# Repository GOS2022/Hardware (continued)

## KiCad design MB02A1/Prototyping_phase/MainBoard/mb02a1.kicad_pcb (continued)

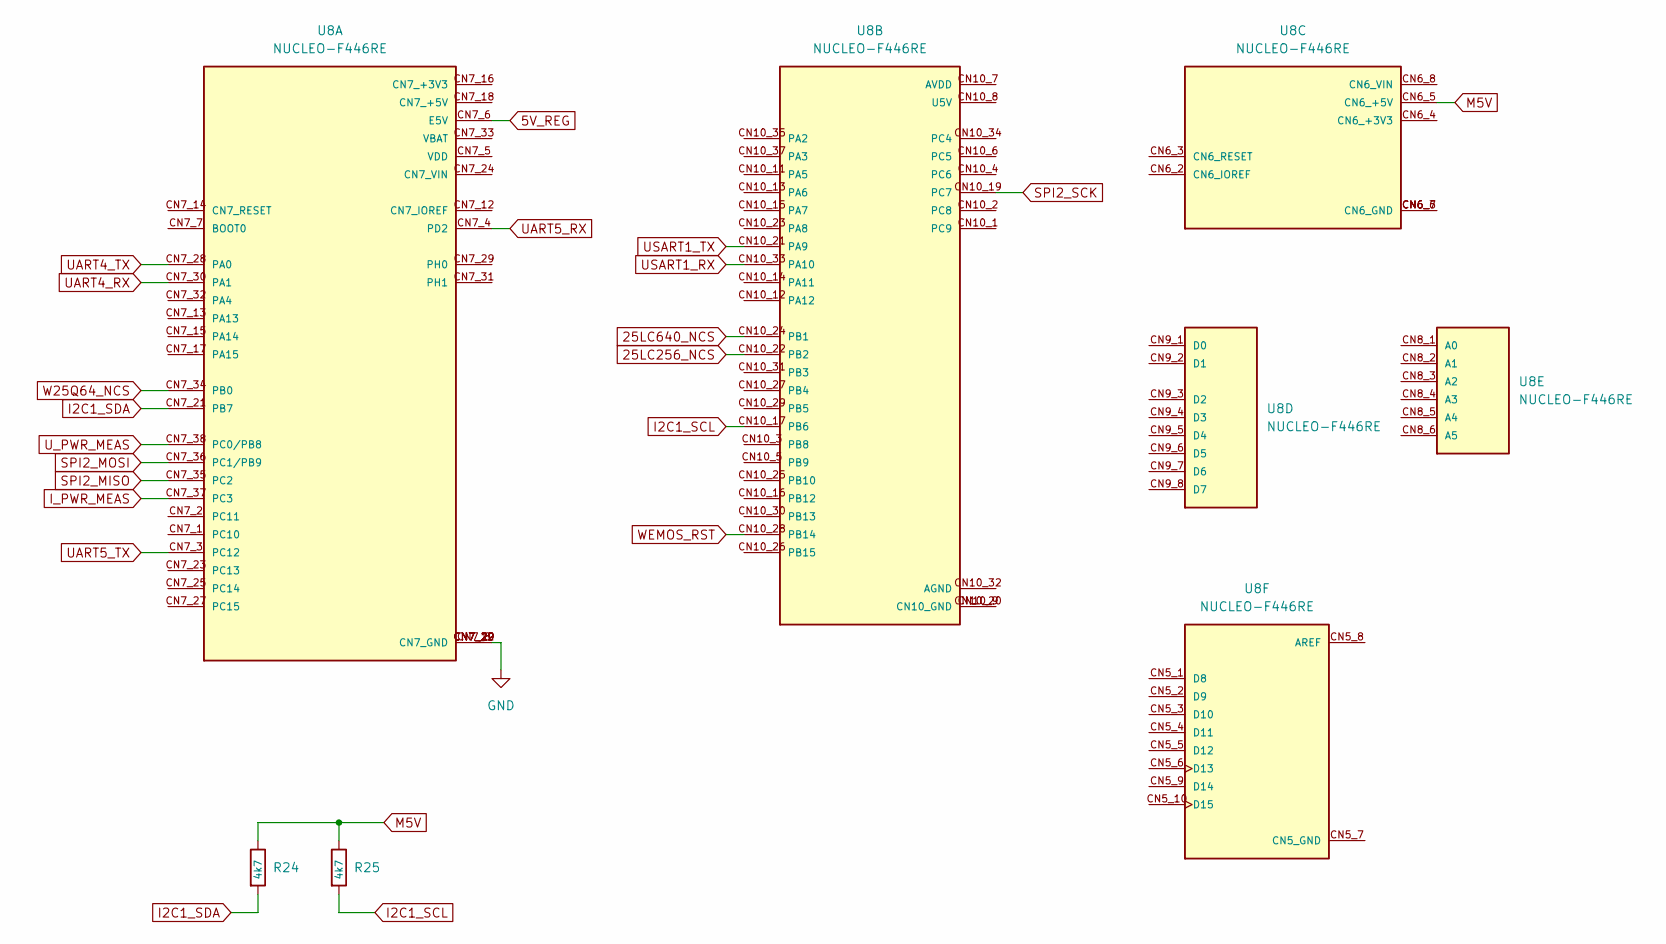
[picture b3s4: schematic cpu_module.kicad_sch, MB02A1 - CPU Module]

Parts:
R24, R25: 4k7; R_0805_2012Metric
U8: NUCLEO-F446RE; MODULE_NUCLEO-F446RE; PARTREV 13; DigiKey_Part_Number 497-15882-ND

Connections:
5V_REG: U8.CN7_6 (E5V); also elsewhere on the board
25LC256_NCS: U8.CN10_22 (PB2); also elsewhere on the board
25LC640_NCS: U8.CN10_24 (PB1); also elsewhere on the board
GND: U8.CN7_8 (CN7_GND), U8.CN7_19 (CN7_GND), U8.CN7_20 (CN7_GND), U8.CN7_22 (CN7_GND); also elsewhere on the board
I2C1_SCL: R25.2, U8.CN10_17 (PB6); also elsewhere on the board
I2C1_SDA: R24.2, U8.CN7_21 (PB7); also elsewhere on the board
I_PWR_MEAS: U8.CN7_37 (PC3); also elsewhere on the board
M5V: R24.1, R25.1, U8.CN6_5 (CN6_+5V); also elsewhere on the board
unnamed: U8.CN10_9 (CN10_GND), U8.CN10_20 (CN10_GND)
unnamed: U8.CN6_6 (CN6_GND), U8.CN6_7 (CN6_GND)
SPI2_MISO: U8.CN7_35 (PC2); also elsewhere on the board
SPI2_MOSI: U8.CN7_36 (PC1/PB9); also elsewhere on the board
SPI2_SCK: U8.CN10_19 (PC7); also elsewhere on the board
UART4_RX: U8.CN7_30 (PA1); also elsewhere on the board
UART4_TX: U8.CN7_28 (PA0); also elsewhere on the board
UART5_RX: U8.CN7_4 (PD2); also elsewhere on the board
UART5_TX: U8.CN7_3 (PC12); also elsewhere on the board
USART1_RX: U8.CN10_33 (PA10); also elsewhere on the board
USART1_TX: U8.CN10_21 (PA9); also elsewhere on the board
U_PWR_MEAS: U8.CN7_38 (PC0/PB8); also elsewhere on the board
W25Q64_NCS: U8.CN7_34 (PB0); also elsewhere on the board
WEMOS_RST: U8.CN10_28 (PB14); also elsewhere on the board

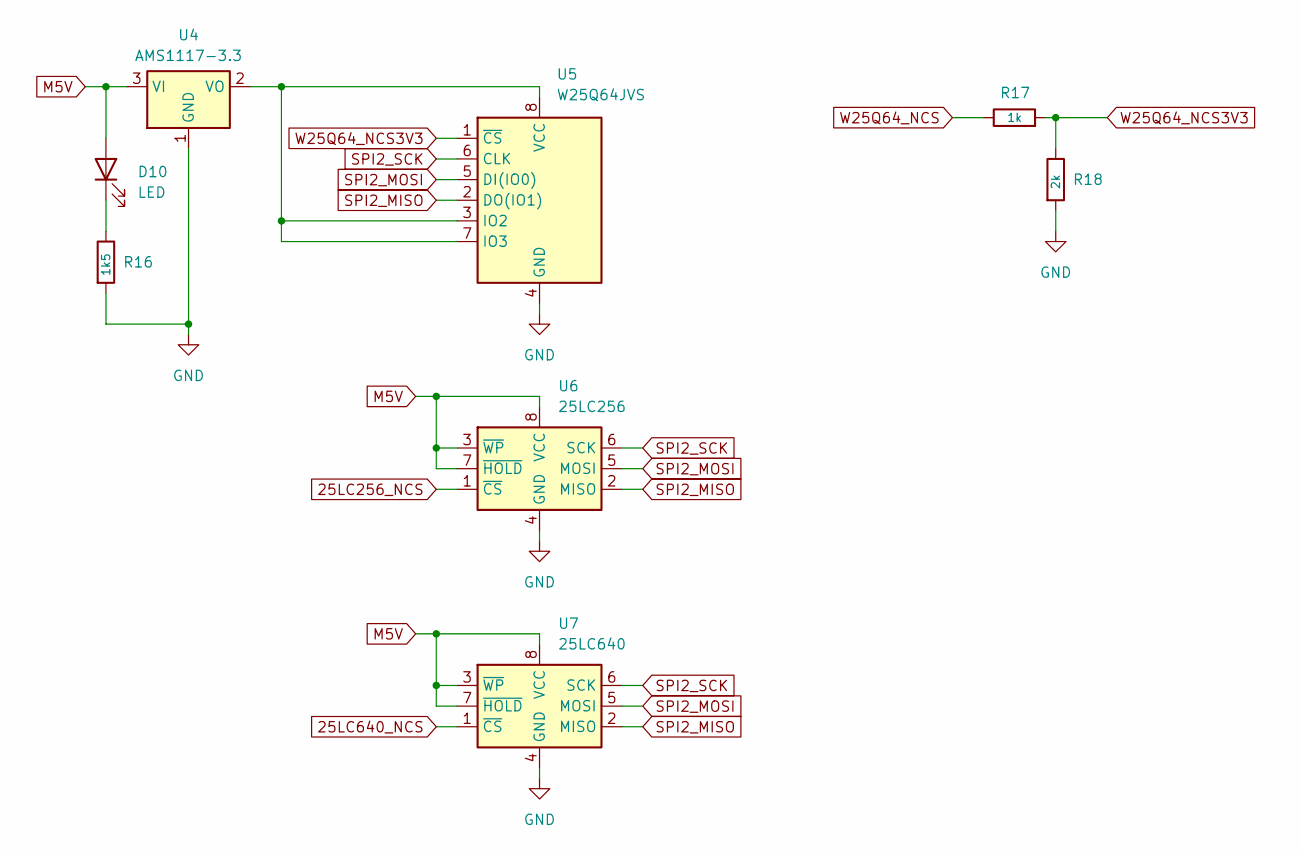
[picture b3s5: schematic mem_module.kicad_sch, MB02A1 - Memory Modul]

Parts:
D10: LED; LED_1206_3216Metric
R16: 1k5; R_0805_2012Metric
R17: 1k; R_0805_2012Metric
R18: 2k; R_0805_2012Metric
U4: AMS1117-3.3; SOT-223-3_TabPin2
U5: W25Q64JVS; SOIC-8_5.23x5.23mm_P1.27mm
U6: 25LC256; SOIC-8_3.9x4.9mm_P1.27mm
U7: 25LC640; SOIC-8_3.9x4.9mm_P1.27mm

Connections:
25LC256_NCS: U6.1 (~CS); also elsewhere on the board
25LC640_NCS: U7.1 (~CS); also elsewhere on the board
GND: R16.2, R18.2, U4.1 (GND), U5.4 (GND), U6.4 (GND), U7.4 (GND); also elsewhere on the board
M5V: D10.2 (A), U4.3 (VI), U6.3 (~WP), U6.7 (~HOLD), U6.8 (VCC), U7.3 (~WP), U7.7 (~HOLD), U7.8 (VCC); also elsewhere on the board
unnamed: D10.1 (K), R16.1
unnamed: U4.2 (VO), U5.3 (IO2), U5.7 (IO3), U5.8 (VCC)
SPI2_MISO: U5.2 (DO(IO1)), U6.2 (MISO), U7.2 (MISO); also elsewhere on the board
SPI2_MOSI: U5.5 (DI(IO0)), U6.5 (MOSI), U7.5 (MOSI); also elsewhere on the board
SPI2_SCK: U5.6 (CLK), U6.6 (SCK), U7.6 (SCK); also elsewhere on the board
W25Q64_NCS: R17.1; also elsewhere on the board
W25Q64_NCS3V3: R17.2, R18.1, U5.1 (~CS)

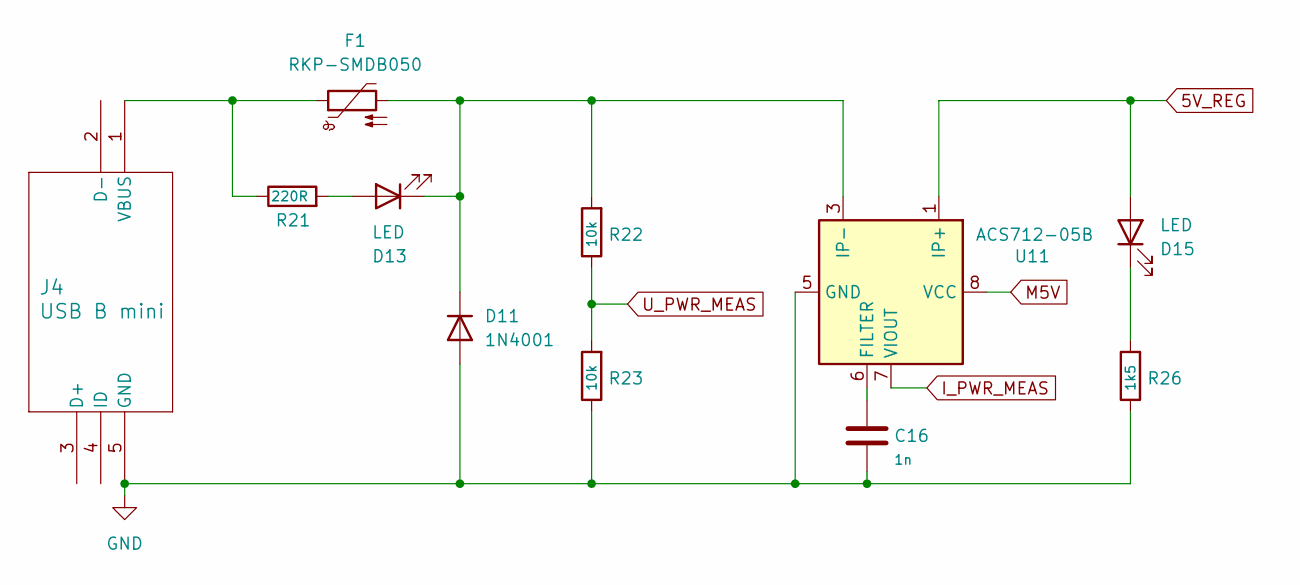
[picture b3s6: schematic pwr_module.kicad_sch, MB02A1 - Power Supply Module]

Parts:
C16: 1n; C_0805_2012Metric
D11: 1N4001; D_DO-41_SOD81_P10.16mm_Horizontal
D13, D15: LED; LED_1206_3216Metric
F1: RKP-SMDB050; R_1206_3216Metric
J4: USB B mini; 54819-0519_MOL
R21: 220R; R_0805_2012Metric
R22, R23: 10k; R_0805_2012Metric
R26: 1k5; R_0805_2012Metric
U11: ACS712-05B; SOIC-8_3.9x4.9mm_P1.27mm

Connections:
5V_REG: D15.2 (A), U11.1 (IP+), U11.2 (IP+); also elsewhere on the board
GND: C16.2, D11.2 (A), J4.5 (GND), R23.1, R26.1, U11.5 (GND); also elsewhere on the board
I_PWR_MEAS: U11.7 (VIOUT); also elsewhere on the board
M5V: U11.8 (VCC); also elsewhere on the board
unnamed: D11.1 (K), D13.1 (K), F1.2, R22.2, U11.3 (IP-), U11.4 (IP-)
unnamed: D13.2 (A), R21.2
unnamed: D15.1 (K), R26.2
unnamed: F1.1, J4.1 (VBUS), R21.1
unnamed: C16.1, U11.6 (FILTER)
U_PWR_MEAS: R22.1, R23.2; also elsewhere on the board

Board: 2 copper layers, 74 parts (0 on the bottom side), 70 nets, no tracks yet.

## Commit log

2024-12-05 PSU01A1 design and production files added.
2024-12-05 MEM01A1 design and production files added.
2024-12-10 Data sheets added.
2024-12-10 Power Supply Module prototype added.
2025-03-24 Design updated.
2025-03-28 Datasheets added, design updated.
2025-04-05 Design update, production preparation.
2025-04-05 Folder structure change, exported files added.
2025-04-09 DS3231 added, backups removed, DS1307 removed.
2025-07-04 MB02A2 added.
2025-07-31 PB01A1 design added.
2025-11-18 Updated,
